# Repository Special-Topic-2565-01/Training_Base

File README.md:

# Training_Base
Training board base

## Components ##

### Temperature and Humidity sensor ###

## Design tool ##

### Kicad ### 
ใช้ Kicad รุ่นล่าสุด
ดาวน์โหลดจากที่นี่
https://www.kicad.org/download/

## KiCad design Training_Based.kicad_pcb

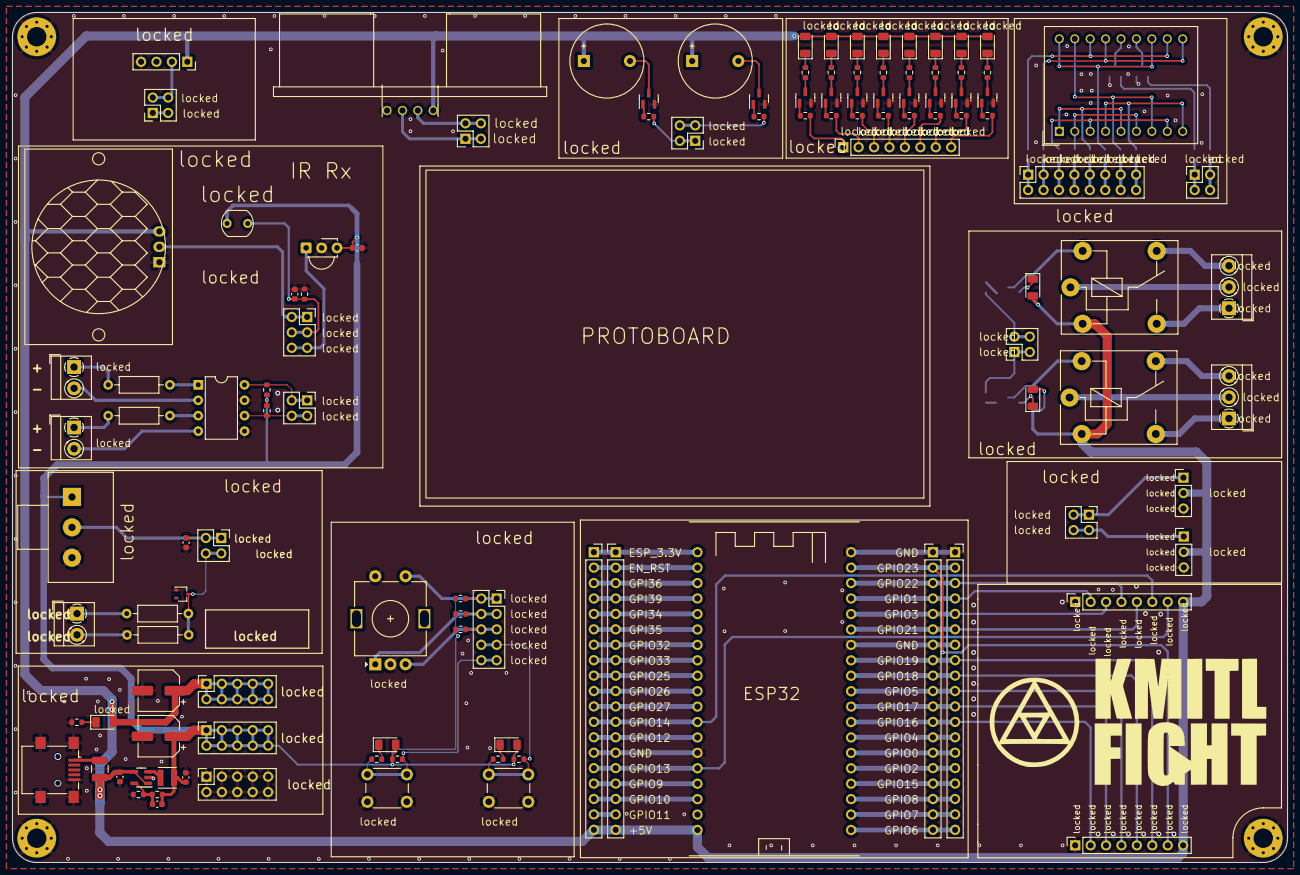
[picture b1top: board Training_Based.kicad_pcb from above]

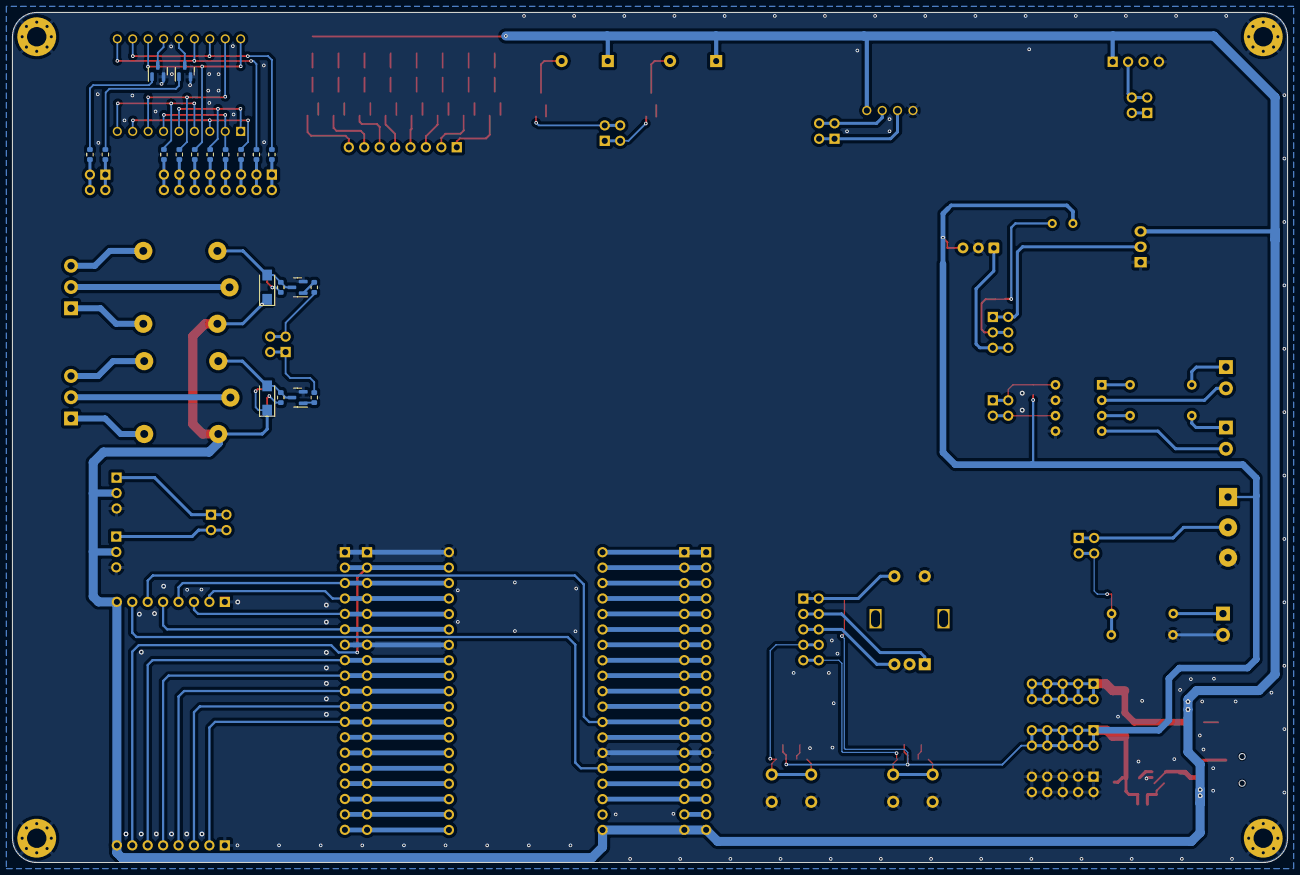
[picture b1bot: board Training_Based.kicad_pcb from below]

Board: 2 copper layers, 210.0 x 140.0 mm, 142 parts (20 on the bottom side), 142 nets.

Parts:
BZ1: Buzzer (IN); Buzzer_12x9.5RM7.6
BZ2: Buzzer (EX); Buzzer_12x9.5RM7.6
C1: 22uF/6.3V; C_0603_1608Metric
C2, C6, C8: 1nF; C_0603_1608Metric
C3, C5: 100uF/35V; CP_Elec_6.3x7.7
C4: 100nF; C_0603_1608Metric
C7: 0.1uF; C_0603_1608Metric
D1, D2: M7; DO-214AC
D3: BZX84C3V3LT1G; SOT-323_SC-70
F1: 3.00A; Fuse_1210_3225Metric
GKMITLLOGO: LOGO; KMITL
GSIETLOGO: LOGO; SIET_15x15
H1, H2, H3, H4: MountingHole_Pad; MountingHole_3.2mm_M3_Pad_Via
J1: ESP32_LEFT_A; PinHeader_1x19_P2.54mm_Vertical
J2: ESP32_LEFT_B; PinSocket_1x19_P2.54mm_Vertical
J3: ESP32_RIGHT_A; PinSocket_1x19_P2.54mm_Vertical
J4: ESP32_RIGHT_B; PinHeader_1x19_P2.54mm_Vertical
J5: LED x8; PinSocket_1x08_P2.54mm_Vertical
J6: TEMP-HUMID; PinSocket_2x02_P2.54mm_Vertical
J7: Ultrasonic; PinSocket_2x02_P2.54mm_Vertical
J8: Buzzer; PinSocket_2x02_P2.54mm_Vertical
J9: RELAY; PinSocket_2x02_P2.54mm_Vertical
J10: 7 Segment Digit; PinSocket_2x08_P2.54mm_Vertical
J11: 7 Segment Common; PinSocket_2x02_P2.54mm_Vertical
J12: SERVO MOTOR; PinSocket_2x02_P2.54mm_Vertical
J13: SERVO 1; PinHeader_1x03_P2.54mm_Vertical
J14: SERVO 2; PinHeader_1x03_P2.54mm_Vertical
J15: OPTO ISOLATOR; PinSocket_2x02_P2.54mm_Vertical
J16: OPTO; PinSocket_2x03_P2.54mm_Vertical
J17: SWITCH; PinSocket_2x05_P2.54mm_Vertical
J18: Analog Input; PinSocket_2x02_P2.54mm_Vertical
J19: USB_B_Mini; USB_Mini-B_Lumberg_2486_01_Horizontal
J20: +5V; PinSocket_2x05_P2.54mm_Vertical
J21: +3.3V; PinSocket_2x05_P2.54mm_Vertical
J22: GND; PinSocket_2x05_P2.54mm_Vertical
J23, J24: Conn_01x08; PinSocket_1x08_P2.54mm_Vertical
K1, K2: FINDER-36.11; Relay_SPDT_Finder_36.11
L1: 2.2uH/1.5A; L_Neosid_SMS-ME3015
LED1, LED2, LED3, LED4, LED5, LED6, LED7, LED8, LED9, LED10, LED11, LED12, LED13: RED 1206; LED_1206_3216Metric
P1: K1; TerminalBlock_MetzConnect_Type059_RT06303HBWC_1x03_P3.50mm_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
P2: K2; TerminalBlock_MetzConnect_Type059_RT06303HBWC_1x03_P3.50mm_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
P3: OPTO INPUT 1; TerminalBlock_MetzConnect_Type059_RT06302HBWC_1x02_P3.50mm_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
P4: OPTO INPUT 2; TerminalBlock_MetzConnect_Type059_RT06302HBWC_1x02_P3.50mm_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
P5: Voltage Input; TerminalBlock_MetzConnect_Type059_RT06302HBWC_1x02_P3.50mm_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
PIR1: PIR_Motion_Sensor; PIR_HC-SR501
Q1, Q2, Q3, Q4, Q5, Q6, Q7, Q8, Q9, Q10, Q11, Q12, Q13, Q14: BC817; SOT-23
R1, R4, R6, R8, R10, R12, R14, R16, R23, R24, R25, R26, R27, R28, R29, R30, R31, R32, R39, R42, R45: 470; R_0603_1608Metric
R2, R3, R5, R7, R9, R11, R13, R15, R17, R18, R38, R40, R41, R48, R49, R50: 10k; R_0603_1608Metric
R19, R20, R21, R22: 4.7k; R_0603_1608Metric
R33, R34: 1k; R_Axial_DIN0207_L6.3mm_D2.5mm_P10.16mm_Horizontal
R35, R36: 47k; R_0603_1608Metric
R37: LDR07; R_LDR_5.1x4.3mm_P3.4mm_Vertical
R43: 100k; R_Axial_DIN0207_L6.3mm_D2.5mm_P10.16mm_Horizontal
R44: 10k; R_Axial_DIN0207_L6.3mm_D2.5mm_P10.16mm_Horizontal
R46: 220k; R_0603_1608Metric
R47: 49.9k; R_0603_1608Metric
RV1: 50kB; Potentiometer_Alps_RK163_Single_Horizontal
SW1: RotaryEncoder_Switch; RotaryEncoder_Alps_EC11E-Switch_Vertical_H20mm
SW2, SW3: SW_Push; SW_PUSH_6mm_H5mm
TH2: DHT22_Temperature_Humidity; PinSocket_1x04_P2.54mm_Vertical
U1: HC-SR04
U2: Protoboard
U3: esp32_38_pins-custom_library; ESP32-DevKitC
U4: DC56-11SURKWA; DA56-11SURKWA
U5: LTV-827; DIP-8_W7.62mm
U6: TSOP382xx; Vishay_MINICAST-3Pin
U7: SY8089AAAC; SOT-23-5

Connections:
+3.3V: C2.1, C3.1, C4.1, C7.1, J21.1, J21.2, J21.3, J21.4, J21.5, J21.6, J21.7, J21.8, J21.9, J21.10, L1.2, LED11.2 (A), LED12.2 (A), R35.2, R36.2, R37.1, R40.1, R41.1, R46.1, R48.1, R49.1, R50.1, RV1.1, U6.3 (Vs)
+5V: BZ1.1 (-), BZ2.1 (-), C1.1, C5.1, D1.1 (K), D2.1 (K), F1.1, J1.19, J2.19, J13.2, J14.2, J20.1, J20.2, J20.3, J20.4, J20.5, J20.6, J20.7, J20.8, J20.9, J20.10, J23.8, J24.8, K1.A1, K2.A1, LED1.2 (A), LED2.2 (A), LED3.2 (A), LED4.2 (A), LED5.2 (A), LED6.2 (A), LED7.2 (A), LED8.2 (A), LED9.2 (A), LED10.2 (A), LED13.2 (A), PIR1.3 (VCC), TH2.1 (VDD), U1.1 (Vcc), U3.19 (5V), U7.1 (EN), U7.4 (IN)
/+3.3V_ESP: J1.1, J2.1, U3.1 (3.3V)
/A_Rotary: J17.3, J17.4, R48.2, SW1.A
/Analog_Input: D3.3 (K), J18.3, J18.4, R43.1, R44.2
/BUZZER1: J8.1, J8.3, R18.1
/BUZZER2: J8.2, J8.4, R17.1
/B_Rotary: J17.5, J17.6, R49.2, SW1.B
/DATA: J6.3, J6.4, TH2.2 (DATA)
/DIG1: J11.1, J11.2, R21.1
/DIG2: J11.3, J11.4, R22.1
/EN_RST: J1.2, J2.2, U3.2 (EN_RST)
/Echo: J7.1, J7.2, U1.3 (Echo)
/GPI34: J1.5, J2.5, U3.5 (GPI34)
/GPI35: J1.6, J2.6, U3.6 (GPI35)
/GPI36: J1.3, J2.3, U3.3 (GPI36)
/GPI39: J1.4, J2.4, U3.4 (GPI39)
/GPIO0: J3.14, J4.14, U3.25 (GPIO0)
/GPIO1: J3.4, J4.4, J23.2, U3.35 (GPIO1)
/GPIO2: J3.15, J4.15, U3.24 (GPIO2)
/GPIO3: J3.5, J4.5, J23.3, U3.34 (GPIO3)
/GPIO4: J3.13, J4.13, U3.26 (GPIO4)
/GPIO5: J3.10, J4.10, J24.4, U3.29 (GPIO5)
/GPIO6: J3.19, J4.19, U3.20 (GPIO6)
/GPIO7: J3.18, J4.18, U3.21 (GPIO7)
/GPIO8: J3.17, J4.17, U3.22 (GPIO8)
/GPIO9: J1.16, J2.16, U3.16 (GPIO9)
/GPIO10: J1.17, J2.17, U3.17 (GPIO10)
/GPIO11: J1.18, J2.18
/GPIO12: J1.13, J2.13, U3.13 (GPIO12)
/GPIO13: J1.15, J2.15, J23.7, U3.15 (GPIO13)
/GPIO14: J1.12, J2.12, J23.6, U3.12 (GPIO14)
/GPIO15: J3.16, J4.16, U3.23 (GPIO15)
/GPIO16: J3.12, J4.12, J24.2, U3.27 (GPIO16)
/GPIO17: J3.11, J4.11, J24.3, U3.28 (GPIO17)
/GPIO18: J3.9, J4.9, J24.5, U3.30 (GPIO18)
/GPIO19: J3.8, J4.8, J24.6, U3.31 (GPIO19)
/GPIO21: J3.6, J4.6, J23.5, U3.33 (GPIO21)
/GPIO22: J3.3, J4.3, J23.4, U3.36 (GPIO22)
/GPIO23: J3.2, J4.2, J24.7, U3.37 (GPIO23)
/GPIO25: J1.9, J2.9, U3.9 (GPIO25)
/GPIO26: J1.10, J2.10, U3.10 (GPIO26)
/GPIO27: J1.11, J2.11, U3.11 (GPIO27)
/GPIO32: J1.7, J2.7, U3.7 (GPIO32)
/GPIO33: J1.8, J2.8, U3.8 (GPIO33)
/IRRX_OUTPUT: J16.5, J16.6, U6.1 (OUT)
/LDR_OUTPUT: C6.1, J16.3, J16.4, R37.2, R38.2
/LED1: J5.1, R2.1
/LED2: J5.2, R3.1
/LED3: J5.3, R5.1
/LED4: J5.4, R7.1
/LED5: J5.5, R9.1
/LED6: J5.6, R11.1
/LED7: J5.7, R13.1
/LED8: J5.8, R15.1
/LX: L1.1, U7.3 (LX)
/PIR_DATA: J16.1, J16.2, PIR1.2 (DATA)
/POTO_OUT1: J15.1, J15.2, R35.1, U5.8
/POTO_OUT2: J15.3, J15.4, R36.1, U5.6
/Poten_voltage: C8.1, J18.1, J18.2, RV1.2
/RELAY1: J9.1, J9.2, R19.1
/RELAY2: J9.3, J9.4, R20.1
/S1_PB: J17.7, J17.8, R39.2, R40.2, SW2.2
/S1_Rotary: J17.1, J17.2, R50.2, SW1.S1
/S2_PB: J17.9, J17.10, R41.2, R42.2, SW3.2
/SEG_A: J10.1, J10.2, R23.1
/SEG_B: J10.3, J10.4, R24.1
/SEG_C: J10.5, J10.6, R25.1
/SEG_D: J10.7, J10.8, R26.1
/SEG_DP: J10.15, J10.16, R30.1
/SEG_E: J10.9, J10.10, R27.1
/SEG_F: J10.11, J10.12, R28.1
/SEG_G: J10.13, J10.14, R29.1
/SERVO1: J12.1, J12.2, J13.1
/SERVO2: J12.3, J12.4, J14.1
/S_A: R23.2, U4.11 (DIG2_A), U4.16 (DIG1_A)
/S_B: R24.2, U4.10 (DIG2_B), U4.15 (DIG1_B)
/S_C: R25.2, U4.3 (DIG1_C), U4.8 (DIG2_C)
/S_D: R26.2, U4.2 (DIG1_D), U4.6 (DIG2_D)
/S_DP: R30.2, U4.4 (DP1), U4.9 (DP2)
/S_E: R27.2, U4.1 (DIG1_E), U4.5 (DIG2_E)
/S_F: R28.2, U4.12 (DIG2_F), U4.18 (DIG1_F)
/S_G: R29.2, U4.7 (DIG2_G), U4.17 (DIG1_G)
/Trig: J7.3, J7.4, U1.2 (Trig)
GND: C1.2, C3.2, C4.2, C5.2, C6.2, C7.2, C8.2, D3.1 (A), H1.1, H2.1, H3.1, H4.1, J1.14, J2.14, J3.1, J3.7, J4.1, J4.7, J13.3, J14.3, J19.5 (GND), J19.6 (Shield), J22.1, J22.2, J22.3, J22.4, J22.5, J22.6, J22.7, J22.8, J22.9, J22.10, J23.1, J24.1, P5.2, PIR1.1 (GND), Q1.2 (E), Q2.2 (E), Q3.2 (E), Q4.2 (E), Q5.2 (E), Q6.2 (E), Q7.2 (E), Q8.2 (E), Q9.2 (E), Q10.2 (E), Q11.2 (E), Q12.2 (E), Q13.2 (E), Q14.2 (E), R38.1, R44.1, R45.2, R47.2, RV1.3, SW1.C, SW1.S2, SW2.1, SW3.1, TH2.4 (GND), U1.4 (Gnd), U3.14 (GND), U3.32 (GND), U3.38 (GND), U5.5, U5.7, U6.2 (GND), U7.2 (GND)
unnamed: BZ1.2 (+), Q1.3 (C)
unnamed: BZ2.2 (+), Q10.3 (C)
unnamed: D1.2 (A), K1.A2, Q11.3 (C), R31.2
unnamed: D2.2 (A), K2.A2, Q12.3 (C), R32.2
unnamed: J6.1, J6.2
unnamed: F1.2, J19.1 (VBUS)
unnamed: LED1.1 (K), R1.1
unnamed: LED2.1 (K), R4.1
unnamed: LED3.1 (K), R6.1
unnamed: LED4.1 (K), R8.1
unnamed: LED5.1 (K), R10.1
unnamed: LED6.1 (K), R12.1
unnamed: LED7.1 (K), R14.1
unnamed: LED8.1 (K), R16.1
unnamed: LED9.1 (K), R31.1
unnamed: LED10.1 (K), R32.1
unnamed: LED11.1 (K), R39.1
unnamed: LED12.1 (K), R42.1
unnamed: LED13.1 (K), R45.1
unnamed: K1.14, P1.1
unnamed: K1.11, P1.2
unnamed: K1.12, P1.3
unnamed: K2.14, P2.1
unnamed: K2.11, P2.2
unnamed: K2.12, P2.3
unnamed: P3.1, R33.1
unnamed: P3.2, U5.2
unnamed: P4.1, R34.1
unnamed: P4.2, U5.4
unnamed: P5.1, R43.2
unnamed: Q1.1 (B), R18.2
unnamed: Q2.1 (B), R2.2
unnamed: Q2.3 (C), R1.2
unnamed: Q3.1 (B), R3.2
unnamed: Q3.3 (C), R4.2
unnamed: Q4.1 (B), R5.2
unnamed: Q4.3 (C), R6.2
unnamed: Q5.1 (B), R7.2
unnamed: Q5.3 (C), R8.2
unnamed: Q6.1 (B), R9.2
unnamed: Q6.3 (C), R10.2
unnamed: Q7.1 (B), R11.2
unnamed: Q7.3 (C), R12.2
unnamed: Q8.1 (B), R13.2
unnamed: Q8.3 (C), R14.2
unnamed: Q9.1 (B), R15.2
unnamed: Q9.3 (C), R16.2
unnamed: Q10.1 (B), R17.2
unnamed: Q11.1 (B), R19.2
unnamed: Q12.1 (B), R20.2
unnamed: Q13.1 (B), R21.2
unnamed: Q13.3 (C), U4.14 (DIG1_CC)
unnamed: Q14.1 (B), R22.2
unnamed: Q14.3 (C), U4.13 (DIG2_CC)
unnamed: R33.2, U5.1
unnamed: R34.2, U5.3
unnamed: C2.2, R46.2, R47.1, U7.5 (FB)

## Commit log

2022-07-21 add spacerx6
2022-07-22 ีWork in Progress
2022-07-22 add esp32 board and 3d model
2022-07-22 work in progress 650723.0501
2022-07-22 WIP 6507230502
2022-07-23 add 3D Model
2022-07-23 7 segment and relay
2022-07-23 opto isolator
2022-07-24 update Optoelectronic parts
2022-07-24 add library
2022-07-24 add tact switch and rotary switch
2022-07-24 finish layout
2022-08-06 add files
2022-08-06 WIP 650806-1532
2022-08-07 Final Check
2022-08-07 Final 650807
2022-08-09 generate gerber
